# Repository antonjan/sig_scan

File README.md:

# sig_scan
This project will scan for rf signals and report them if there is signals detected using an rtl-sdr dongle on a a Raspberry Pi<br>
Libraery with exsyended frequency is avalable here https://github.com/librtlsdr/librtlsdr/tree/development<br>
## Pre Req libraeriies
    sudo apt-get install build-essential cmake git
    sudo apt-get install libusb-dev libusb-1.0-0-dev
    git clone https://github.com/librtlsdr/librtlsdr/tree/development
    cd librtlsdr
    git checkout development
    git status

    mkdir build && cd build
    cmake ../ -DINSTALL_UDEV_RULES=ON
    make

    sudo make install
    sudo ldconfig
# Setting up python 
    cd Documents/SX126X_LoRa_HAT_Code/raspberrypi/python/
## Sender 
    source ~/sdr-env/bin/activate
## Receiver
    source venv/bin/activate
# Running SIG Scanner
python gsm_scanner_new2.py

# Rafial R828D pin conections

    R828D (R820T-compatible) Pinout: Pin Number to Name

The R828D is usually supplied in a 32-pin QFN package. Here’s the most commonly reported pinout:

        Pin	Name	Function
        1	VCC	Power supply
        2	VCO	PLL VCO
        3	VCOIN	PLL VCO input
        4	VCOGND	PLL VCO ground
        5	VCOBUF	PLL VCO buffer output
        6	XIN	Crystal oscillator input
        7	XOUT	Crystal oscillator out
        8	VCC	Power supply
        9	GND	Ground
        10	AGC	Automatic Gain Control
        11	IFOUT	Intermediate Frequency Output
        12	VCC	Power supply
        13	GND	Ground
        14	RF_IN	RF Input (from antenna)
        15	GND	Ground
        16	NC	Not Connected
        17	VCC	Power supply
        18	NC	Not Connected
        19	LNA	Low Noise Amp control
        20	VCC	Power supply
        21	GND	Ground
        22	NC	Not Connected
        23	SDA	I²C Data
        24	SCL	I²C Clock
        25	GND	Ground
        26	VCC	Power supply
        27	NC	Not Connected
        28	VCC	Power supply
        29	NC	Not Connected
        30	NC	Not Connected
        31	NC	Not Connected
        32	NC	Not Connected
        30	NC	Not Connected
        31	NC	Not Connected
        32	NC	Not Connected
## Basic Connections

    Antenna → Matching Network → Pin 14 (RF_IN)
    Pin 11 (IFOUT) → RTL2832U IF Input
    Pin 23 (SDA) & Pin 24 (SCL) → RTL2832U I²C (for control)
    Pin 6 (XIN) & Pin 7 (XOUT) → 16 MHz Crystal (one end to XIN, other to XOUT, with load capacitors to GND)
    All VCC Pins → 3.3V Power
    All GND Pins → Ground Plane

## Register Map (Community Reference, RTL-SDR Driver)

The R828D is controlled via I²C. The register map is not openly published, but the rtl-sdr driver configures it as follows:

    I²C Address: 0x8C (write), 0x8D (read)
    Registers:
        Reg 0x00: Tuner enable, AGC, LNA setting
        Reg 0x01–0x05: PLL and frequency control
        Reg 0x06–0x0D: IF settings, filter bandwidth, gain stages
        Reg 0x0E–0x1F: Misc control, calibration, test modes

Example I²C Write Sequence for Initialization:
    
    uint8_t init_regs[] = {
    0x01, 0x16, 0xE0, 0x60, 0x40, // PLL settings
    0x20, 0x80, 0x40,             // IF gain, filter
    0xA1, 0x4B, 0x10              // AGC, LNA, etc.
    };
    i2c_write(R828D_ADDR, init_regs, sizeof(init_regs));
The actual values depend on frequency, IF, and gain requirements.
Refer to rtl-sdr tuner_r820t.c for full register programming examples. https://github.com/osmocom/rtl-sdr/blob/master/src/tuner_r820t.c

Step-by-Step Build Guide

    Connect RF_IN (Pin 14) to antenna/matching network.
    Connect IFOUT (Pin 11) to RTL2832U IF Input.
    Connect SDA (Pin 23) and SCL (Pin 24) to RTL2832U I²C bus. Use pull-up resistors (~4.7kΩ) to 3.3V.
    Connect 16 MHz crystal between XIN (Pin 6) and XOUT (Pin 7), with recommended load capacitors (~22pF) to ground.
    Connect all VCC pins to regulated 3.3V supply.
    Connect all GND pins to system ground.
    AGC (Pin 10) and LNA (Pin 19) can be controlled by RTL2832U or tied appropriately.
    Initialize R828D via I²C using register sequences from open-source drivers.
# R828 c driver 
https://github.com/osmocom/rtl-sdr/blob/master/src/tuner_r82xx.c

    Pin 10 (AGC) → RTL2832U AGC Output (optional, for gain control)
    Pin 19 (LNA) → Can be tied HIGH or controlled by RTL2832U for LNA operation

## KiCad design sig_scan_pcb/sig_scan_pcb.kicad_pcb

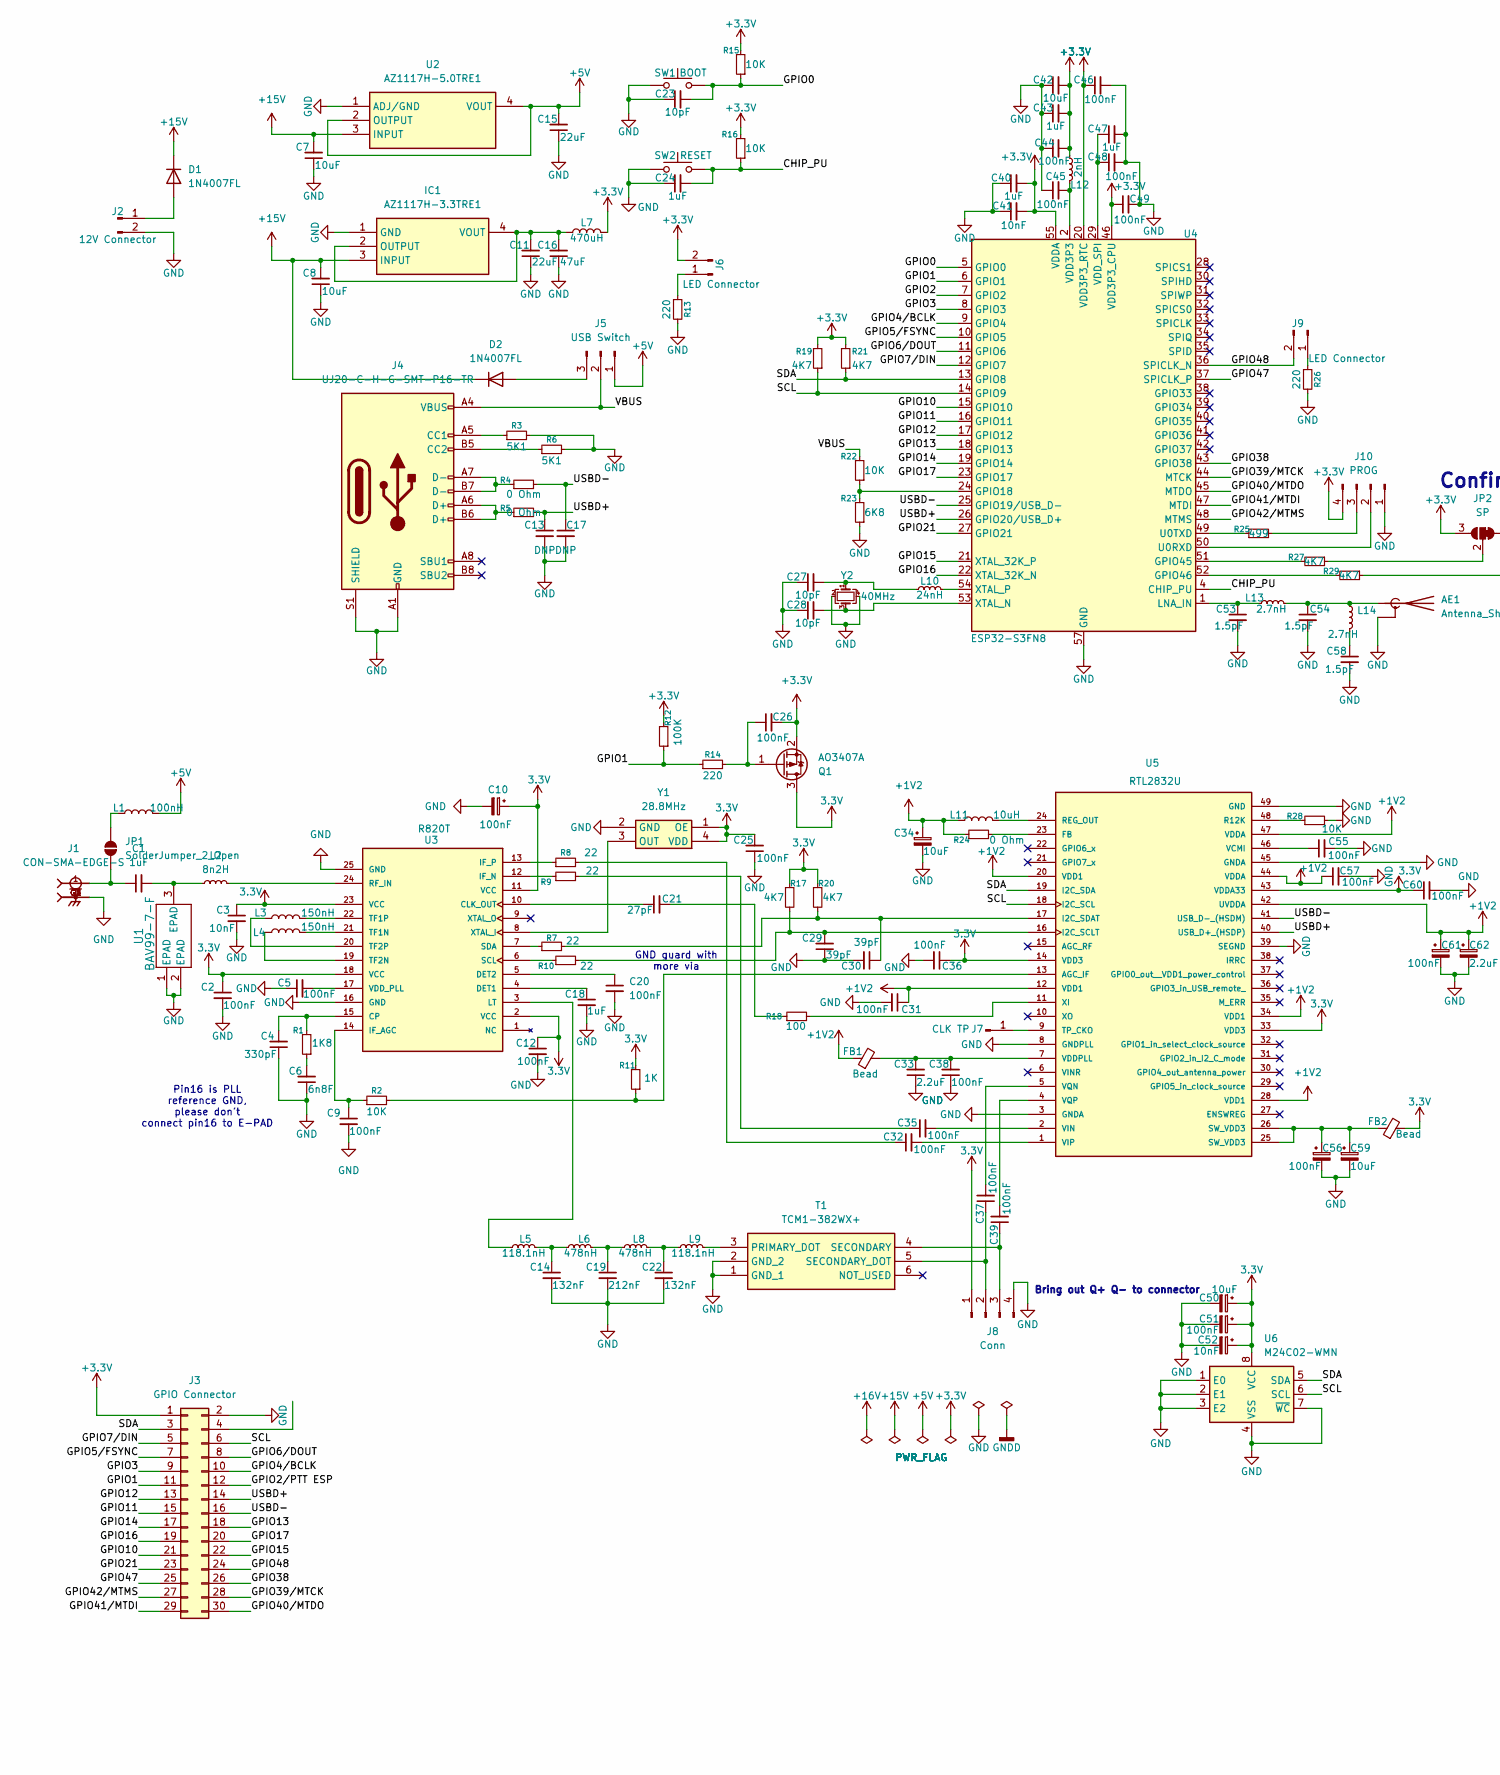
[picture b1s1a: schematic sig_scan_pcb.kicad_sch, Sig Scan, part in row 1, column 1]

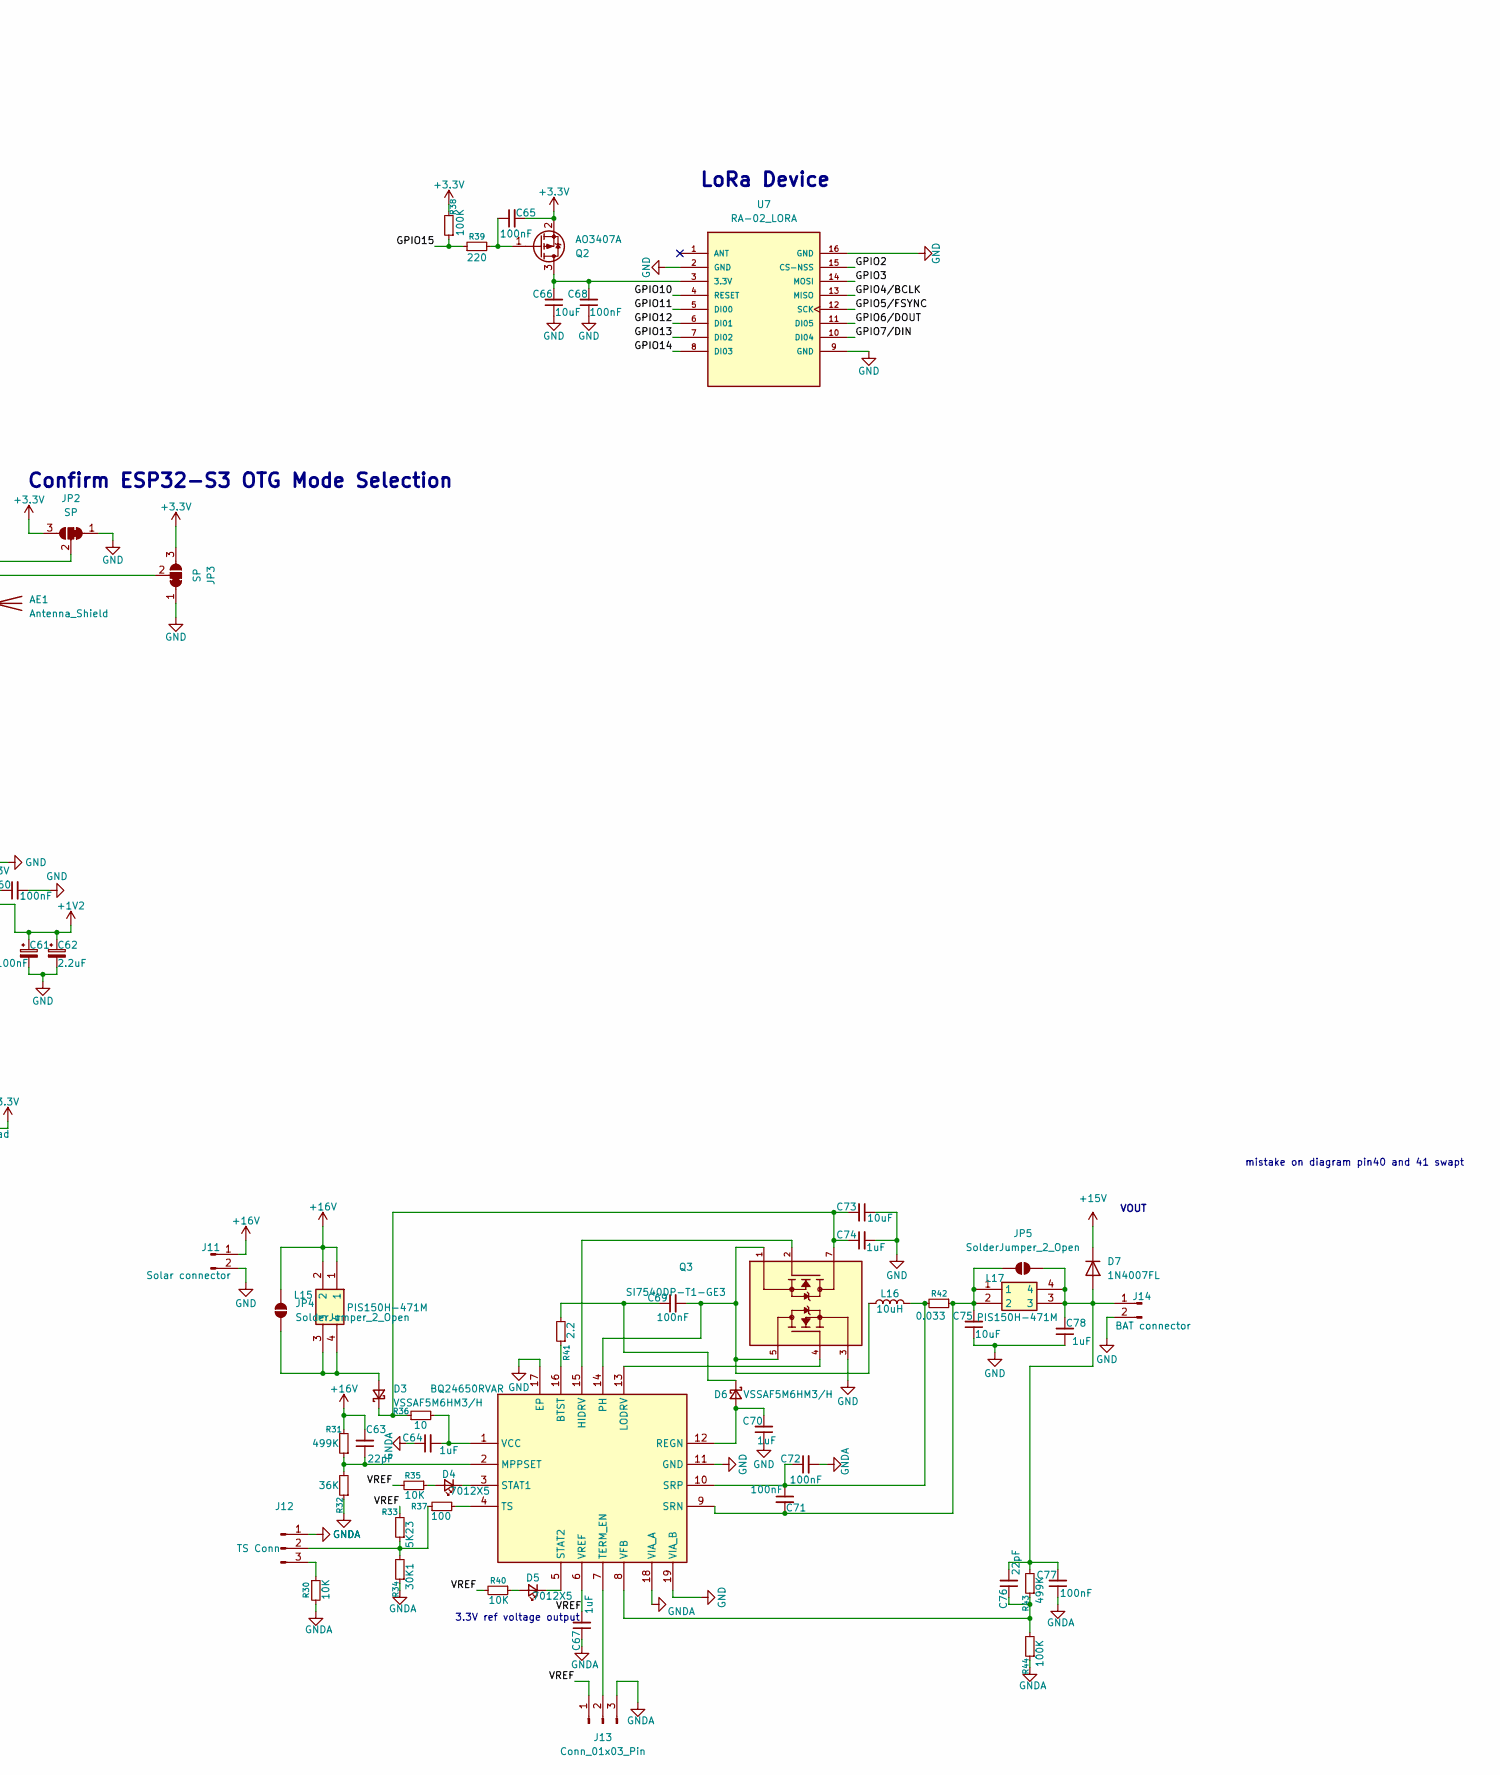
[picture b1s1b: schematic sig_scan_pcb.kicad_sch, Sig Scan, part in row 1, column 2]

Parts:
AE1: Antenna_Shield; Texas_SWRA117D_2.4GHz_Left
C1, C18, C24, C40, C43, C47, C64, C67, C70, C74, C78: 1uF; C_0805_2012Metric
C2, C5, C9, C10, C12, C20, C25, C26, C31, C32, C35, C36, C37, C38, C39, C44, C45, C46, C48, C49, C51, C55, C56, C57, C60, C61, C65, C68, C69, C71, C72, C77: 100nF; C_0805_2012Metric
C3, C41, C52: 10nF; C_0805_2012Metric
C4: 330pF; C_0805_2012Metric
C6: 6n8F; C_0805_2012Metric
C7, C8, C34, C42, C50, C59, C66, C73, C75: 10uF; C_0805_2012Metric
C11, C15: 22uF; C_0805_2012Metric
C13, C17: DNP; C_0805_2012Metric
C14, C22: 132nF; C_0805_2012Metric
C16: 47uF; C_1206_3216Metric
C19: 212nF; C_0805_2012Metric
C21: 27pF; C_0805_2012Metric
C23, C27, C28: 10pF; C_0805_2012Metric
C29, C30: 39pF; C_0805_2012Metric
C33, C62: 2.2uF; C_0805_2012Metric
C53, C54, C58: 1.5pF; C_0805_2012Metric
C63, C76: 22pF; C_0805_2012Metric
D1, D2, D7: 1N4007FL; D_SOD-123
D3, D6: VSSAF5M6HM3/H; D_SMA
D4, D5: 7012X5; LED_0805_2012Metric
FB1, FB2: Bead; C_0805_2012Metric
IC1: AZ1117H-3.3TRE1; SOT230P700X180-4N; Mouser Part Number 621-AZ1117H-3.3TRE1
IC2: BQ24650RVAR; QFN50P350X350X100-17N-D; Mouser Part Number 595-BQ24650RVAR
J1: CON-SMA-EDGE-S; RFSOLUTIONS_CON-SMA-EDGE-S; PARTREV 1
J2: 12V Connector; CUI_TB007-508-02BE
J3: GPIO Connector; PinHeader_2x15_P2.54mm_Vertical
J4: UJ20-C-H-G-SMT-P16-TR; USB_C_Receptacle_G-Switch_GT-USB-7010ASV
J5: USB Switch; PinHeader_1x03_P2.54mm_Vertical
J6, J9: LED Connector; PinHeader_1x02_P2.54mm_Vertical
J7: CLK TP; PinHeader_1x01_P2.54mm_Vertical
J8: Conn; PinHeader_1x04_P2.54mm_Vertical
J10: PROG; PinHeader_1x04_P2.54mm_Vertical
J11: Solar connector; CUI_TB007-508-02BE
J12: TS Conn; PinHeader_1x03_P2.54mm_Vertical
J13: Conn_01x03_Pin; SolderJumper-3_P1.3mm_Bridged12_RoundedPad1.0x1.5mm
J14: BAT connector; CUI_TB007-508-02BE
JP1, JP4, JP5: SolderJumper_2_Open; SolderJumper-2_P1.3mm_Open_RoundedPad1.0x1.5mm
JP2, JP3: SP; SolderJumper-3_P1.3mm_Bridged12_RoundedPad1.0x1.5mm
L1: 100nH; L_0805_2012Metric
L2: 8n2H; L_0805_2012Metric
L3, L4: 150nH; L_0805_2012Metric
L5, L9: 118.1nH; L_0603_1608Metric
L6, L8: 478nH; L_0603_1608Metric
L7: 470uH; SRR12604R7Y
L10: 24nH; L_0805_2012Metric
L11: 10uH; L_0805_2012Metric
L12: 2nH; L_0603_1608Metric
L13, L14: 2.7nH; L_0805_2012Metric
L15, L17: PIS150H-471M; PIS150H471M; Mouser Part Number 871-PIS150H-471M
L16: 10uH; IND_IHLP_2525_CZ_VIS
Q1, Q2: AO3407A; SOT-23
Q3: SI7540DP-T1-GE3; TRANS_SI7540DP-T1-GE3; PARTREV 16MAY13
R1: 1K8; R_0805_2012Metric
R2, R15, R16, R22, R28, R30, R35, R40: 10K; R_0805_2012Metric
R3, R6: 5K1; R_0805_2012Metric
R4, R5, R24: 0 Ohm; R_0805_2012Metric
R7, R8, R9, R10: 22; R_0805_2012Metric
R11: 1K; R_0805_2012Metric
R12, R38, R44: 100K; R_0805_2012Metric
R13, R14, R26, R39: 220; R_0805_2012Metric
R17, R19, R20, R21, R27, R29: 4K7; R_0805_2012Metric
R18, R37: 100; R_0805_2012Metric
R23: 6K8; R_0805_2012Metric
R25: 499; R_0805_2012Metric
R31, R43: 499K; R_0805_2012Metric
R32: 36K; R_0805_2012Metric
R33: 5K23; R_0805_2012Metric
R34: 30K1; R_0805_2012Metric
R36: 10; R_0805_2012Metric
R41: 2.2; R_0805_2012Metric
R42: 0.033; R_1206_3216Metric
SW1: BOOT; SW_Tactile_SPST_NO_Straight_CK_PTS636Sx25SMTRLFS
SW2: RESET; SW_Tactile_SPST_NO_Straight_CK_PTS636Sx25SMTRLFS
T1: TCM1-382WX+; TCM1382WX; Mouser Part Number 139-TCM1-382WX
U1: BAV99-7-F; SOT-23_DIO
U2: AZ1117H-5.0TRE1; SOT230P700X180-4N; Mouser Part Number 621-AZ1117H-5.0TRE1
U3: R820T; QFN50P400X400X90-25N; PARTREV 1.2
U4: ESP32-S3FN8; QFN-56-1EP_7x7mm_P0.4mm_EP4x4mm
U5: RTL2832U; QFN40P600X600X100-49N; PARTREV 1.4
U6: M24C02-WMN; SOIC-8_3.9x4.9mm_P1.27mm
U7: RA-02_LORA; MODULE_RA-02_LORA; PARTREV 2018/03/02
Y1: 28.8MHz; ATX11F32000MHZF05T; Mouser Part Number 815-ATX11F32000MF05T
Y2: 40MHz; ABM810000MHZ12D2W

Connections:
3.3V: C2.1, C3.1, C10.1, C12.1, C25.2, C36.1, C50.1, C51.1, C52.1, C60.1, FB2.2, J8.1, Q1.3 (D), R11.2, R17.1, R20.1, U3.2 (VCC), U3.11 (VCC), U3.18 (VCC), U3.23 (VCC), U5.14 (VDD3), U5.33 (VDD3), U5.43 (VDDA33), U6.8 (VCC), Y1.1 (OE), Y1.4 (VDD)
+1V2: C31.1, C34.1, C57.1, C61.1, C62.1, FB1.1, L11.1, R24.1, U5.12 (VDD1), U5.20 (VDD1), U5.28 (VDD1), U5.34 (VDD1), U5.42 (UVDDA), U5.44 (VDDA), U5.47 (VDDA)
+3.3V: C26.2, C40.2, C41.2, C42.2, C43.2, C44.2, C46.1, C49.1, C65.2, J3.1, J6.2, J10.4, JP2.3 (B), JP3.3 (B), L7.2, L12.1, Q1.2 (S), Q2.2 (S), R12.2, R15.2, R16.2, R19.2, R21.2, R38.2, U4.20 (VDD3P3_RTC), U4.46 (VDD3P3_CPU), U4.55 (VDDA), U4.56 (VDDA)
+5V: C15.2, J5.1, L1.2, U2.2 (OUTPUT), U2.4 (VOUT)
+15V: C7.2, C8.2, D1.1 (K), D2.1 (K), D7.1 (K), IC1.3 (INPUT), U2.3 (INPUT)
+16V: C63.2, J11.1, JP4.2 (B), L15.1, L15.2, R31.2
/CHIP_PU: C24.2, R16.1, SW2.2, U4.4 (CHIP_PU)
/GPIO0: C23.2, R15.1, SW1.2, U4.5 (GPIO0)
/GPIO1: J3.11, R12.1, R14.1, U4.6 (GPIO1)
/GPIO2: U4.7 (GPIO2), U7.15 (CS-NSS)
/GPIO3: J3.9, U4.8 (GPIO3), U7.14 (MOSI)
/GPIO4/BCLK: J3.10, U4.9 (GPIO4), U7.13 (MISO)
/GPIO5/FSYNC: J3.7, U4.10 (GPIO5), U7.12 (SCK)
/GPIO6/DOUT: J3.8, U4.11 (GPIO6), U7.11 (DI05)
/GPIO7/DIN: J3.5, U4.12 (GPIO7), U7.10 (DI04)
/GPIO10: J3.21, U4.15 (GPIO10), U7.4 (RESET)
/GPIO11: J3.15, U4.16 (GPIO11), U7.5 (DI00)
/GPIO12: J3.13, U4.17 (GPIO12), U7.6 (DI01)
/GPIO13: J3.18, U4.18 (GPIO13), U7.7 (DI02)
/GPIO14: J3.17, U4.19 (GPIO14), U7.8 (DI03)
/GPIO15: J3.22, R38.1, R39.1, U4.21 (XTAL_32K_P)
/GPIO16: J3.19, U4.22 (XTAL_32K_N)
/GPIO17: J3.20, U4.23 (GPIO17)
/GPIO21: J3.23, U4.27 (GPIO21)
/GPIO38: J3.26, U4.43 (GPIO38)
/GPIO39/MTCK: J3.28, U4.44 (MTCK)
/GPIO40/MTDO: J3.30, U4.45 (MTDO)
/GPIO41/MTDI: J3.29, U4.47 (MTDI)
/GPIO42/MTMS: J3.27, U4.48 (MTMS)
/GPIO47: J3.25, U4.37 (SPICLK_P)
/GPIO48: J3.24, J9.2, U4.36 (SPICLK_N)
/SCL: J3.6, R19.1, U4.14 (GPIO9), U5.18 (I2C_SCL), U6.6 (SCL)
/SDA: J3.3, R21.1, U4.13 (GPIO8), U5.19 (I2C_SDA), U6.5 (SDA)
/USBD+: C13.1, J3.14, R5.2, U4.26 (GPIO20/USB_D+), U5.40 (USB_D+_(HSDP))
/USBD-: C17.1, J3.16, R4.2, U4.25 (GPIO19/USB_D-), U5.41 (USB_D−_(HSDM))
/VBUS: J4.A4 (VBUS), J4.A9 (VBUS), J4.B4 (VBUS), J4.B9 (VBUS), J5.2, R22.2
/VREF: C67.2, IC2.6 (VREF), J13.1, R33.2, R35.2, R40.2
GND: AE1.2 (Shield), C2.2, C3.2, C4.1, C5.1, C6.1, C7.1, C8.1, C9.2, C10.2, C11.1, C12.2, C13.2, C14.2, C15.1, C16.1, C17.2, C18.2, C19.2, C20.2, C22.2, C23.1, C24.1, C25.1, C27.1, C28.1, C29.1, C30.2, C31.2, C33.1, C34.2, C36.2, C38.1, C40.1, C41.1, C42.1, C43.1, C44.1, C45.1, C46.2, C47.2, C48.2, C49.2, C50.2, C51.2, C52.2, C53.2, C54.2, C55.2, C56.2, C57.2, C58.2, C59.2, C60.2, C61.2, C62.2, C66.1, C68.1, C70.1, C73.1, C74.2, C75.1, C78.1, IC1.1 (GND), IC2.11 (GND), IC2.17 (EP), IC2.19 (VIA_B), J1.G1, J1.G2, J1.G3, J1.G4, J2.2, J3.2, J4.A1 (GND), J4.A12 (GND), J4.B1 (GND), J4.B12 (GND), J4.S1 (SHIELD), J8.4, J10.1, J11.2, J14.2, JP2.1 (A), JP3.1 (A), Q3.3, R3.2, R6.2, R13.2, R23.1, R26.2, R28.2, SW1.1, SW2.1, T1.1 (GND_1), T1.2 (GND_2), U1.1 (EPAD), U1.2 (EPAD), U2.1 (ADJ/GND), U3.16 (GND), U3.25 (GND), U4.57 (GND), U5.3 (GNDA), U5.8 (GNDPLL), U5.39 (SEGND), U5.45 (GNDA), U5.49 (GND), U6.1 (E0), U6.2 (E1), U6.3 (E2), U6.4 (VSS), U6.7 (~WC), U7.2 (GND), U7.9 (GND), U7.16 (GND), Y1.2 (GND), Y2.2, Y2.4
GNDA: C64.1, C67.1, C72.2, C77.1, IC2.18 (VIA_A), J12.1, J13.3, R30.2, R32.1, R34.1, R44.1
unnamed: AE1.1 (A), C54.1, L13.2, L14.1
unnamed: C1.2, L2.1, U1.3 (EPAD)
unnamed: C6.2, R1.1
unnamed: C14.1, L5.2, L6.1
unnamed: C19.1, L6.2, L8.1
unnamed: C21.2, R18.1
unnamed: C22.1, L8.2, L9.1
unnamed: C27.2, L10.1, Y2.1
unnamed: C32.1, R8.2
unnamed: C35.1, R9.2
unnamed: C45.2, L12.2, U4.2 (VDD3P3), U4.3 (VDD3P3)
unnamed: C56.1, C59.1, FB2.1, U5.25 (SW_VDD3), U5.26 (SW_VDD3)
unnamed: C58.1, L14.2
unnamed: D1.2 (A), J2.1
unnamed: D2.2 (A), J5.3
unnamed: D3.2 (A), JP4.1 (A), L15.3, L15.4
unnamed: C73.2, C74.1, D3.1 (K), Q3.7, Q3.8, Q3.9, R36.1
unnamed: D4.2 (A), R35.1
unnamed: D4.1 (K), IC2.3 (STAT1)
unnamed: D5.2 (A), R40.1
unnamed: D5.1 (K), IC2.5 (STAT2)
unnamed: C70.2, D6.2 (A), IC2.12 (REGN)
unnamed: C69.1, D6.1 (K), R41.2
unnamed: C76.2, C77.2, C78.2, D7.2 (A), J14.1, JP5.1 (A), L17.3, L17.4, R43.2
unnamed: C11.2, C16.2, IC1.2 (OUTPUT), IC1.4 (VOUT), L7.1
unnamed: IC2.16 (BTST), R41.1
unnamed: IC2.15 (HIDRV), Q3.2
unnamed: IC2.13 (LODRV), Q3.4
unnamed: C63.1, IC2.2 (MPPSET), R31.1, R32.2
unnamed: C69.2, IC2.14 (PH), L16.1, Q3.1, Q3.5, Q3.6, Q3.10
unnamed: C71.2, C75.2, IC2.9 (SRN), JP5.2 (B), L17.1, L17.2, R42.1
unnamed: C71.1, C72.1, IC2.10 (SRP), L16.2, R42.2
unnamed: IC2.7 (TERM_EN), J13.2
unnamed: IC2.4 (TS), R37.2
unnamed: C64.2, IC2.1 (VCC), R36.2
unnamed: C76.1, IC2.8 (VFB), R43.1, R44.2
unnamed: J4.A5 (CC1), R3.1
unnamed: J4.B5 (CC2), R6.1
unnamed: J4.A6 (D+), J4.B6 (D+), R5.1
unnamed: J4.A7 (D-), J4.B7 (D-), R4.1
unnamed: J6.1, R13.1
unnamed: J7.1, U5.9 (TP_CKO)
unnamed: C37.1, J8.2, T1.5 (SECONDARY_DOT)
unnamed: C39.1, J8.3, T1.4 (SECONDARY)
unnamed: J9.1, R26.1
unnamed: J10.2, U4.50 (U0RXD)
unnamed: J10.3, R25.2
unnamed: J12.2, R33.1, R34.2, R37.1
unnamed: J12.3, R30.1
unnamed: C1.1, J1.1, JP1.1 (A)
unnamed: JP1.2 (B), L1.1
unnamed: JP2.2 (C), R27.1
unnamed: JP3.2 (C), R29.1
unnamed: C26.1, Q1.1 (G), R14.2
unnamed: C66.2, C68.2, Q2.3 (D), U7.3 (3.3V)
unnamed: C65.1, Q2.1 (G), R39.2
unnamed: L9.2, T1.3 (PRIMARY_DOT)
unnamed: C21.1, U3.10 (CLK_OUT)
unnamed: C4.2, R1.2, U3.15 (CP)
unnamed: C18.1, U3.4 (DET1)
unnamed: C20.1, U3.5 (DET2)
unnamed: C9.1, R2.1, U3.14 (IF_AGC)
unnamed: R9.1, U3.12 (IF_N)
unnamed: R8.1, U3.13 (IF_P)
unnamed: L5.1, U3.3 (LT)
unnamed: L2.2, U3.24 (RF_IN)
unnamed: R10.1, U3.6 (SCL)
unnamed: R7.1, U3.7 (SDA)
unnamed: L4.2, U3.21 (TF1N)
unnamed: L3.2, U3.22 (TF1P)
unnamed: L4.1, U3.19 (TF2N)
unnamed: L3.1, U3.20 (TF2P)
unnamed: C5.2, U3.17 (VDD_PLL)
unnamed: U3.8 (XTAL_I), Y1.3 (OUT)
unnamed: R22.1, R23.2, U4.24 (GPIO18)
unnamed: R27.2, U4.51 (GPIO45)
unnamed: R29.2, U4.52 (GPIO46)
unnamed: C53.1, L13.1, U4.1 (LNA_IN)
unnamed: R25.1, U4.49 (U0TXD)
unnamed: C47.1, C48.1, U4.29 (VDD_SPI)
unnamed: C28.2, U4.53 (XTAL_N), Y2.3
unnamed: L10.2, U4.54 (XTAL_P)
unnamed: R2.2, R11.1, U5.13 (AGC_IF)
unnamed: R24.2, U5.23 (FB)
unnamed: C29.2, R10.2, R17.2, U5.16 (I2C_SCLT)
unnamed: C30.1, R7.2, R20.2, U5.17 (I2C_SDAT)
unnamed: R28.1, U5.48 (R12K)
unnamed: L11.2, U5.24 (REG_OUT)
unnamed: C55.1, U5.46 (VCMI)
unnamed: C33.2, C38.2, FB1.2, U5.7 (VDDPLL)
unnamed: C35.2, U5.2 (VIN)
unnamed: C32.2, U5.1 (VIP)
unnamed: C37.2, U5.5 (VQN)
unnamed: C39.2, U5.4 (VQP)
unnamed: R18.2, U5.11 (XI)

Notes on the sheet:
LoRa Device
Bring out Q+ Q- to connector
VOUT
3.3V ref voltage output
Pin16 is PLL reference GND, please don't connect pin16 to E-PAD
mistake on diagram pin40 and 41 swapt
GND guard with more via
Confirm ESP32-S3 OTG Mode Selection

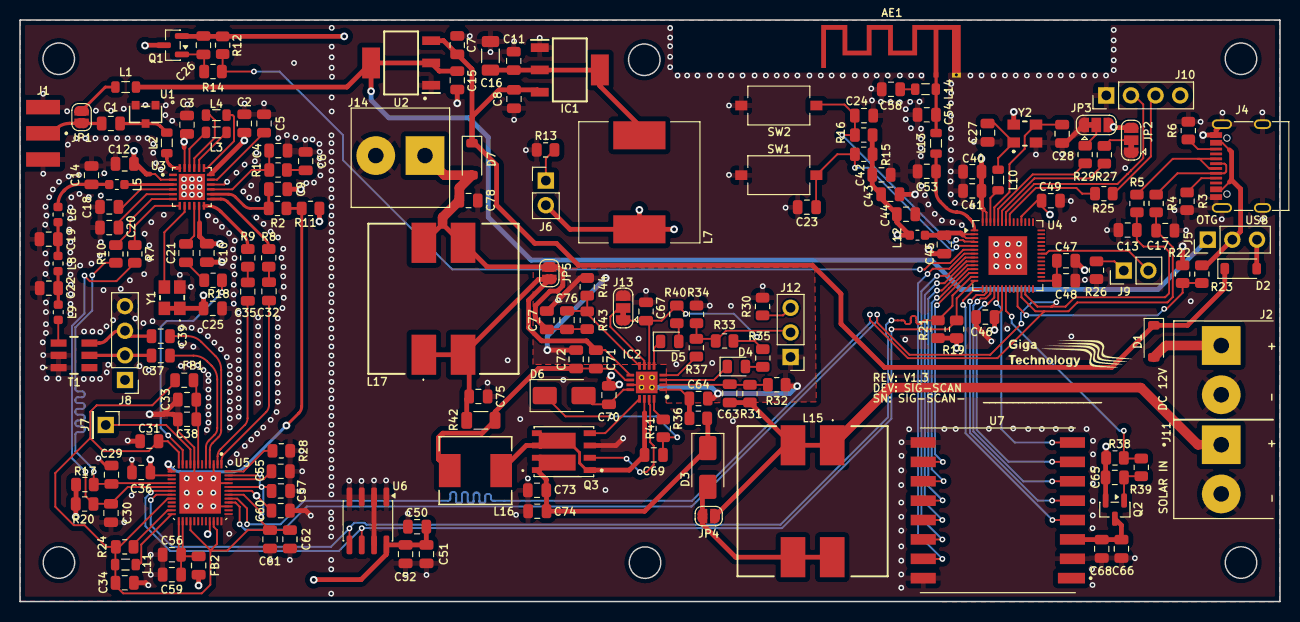
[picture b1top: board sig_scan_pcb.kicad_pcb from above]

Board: 4 copper layers, 130.0 x 60.0 mm, 184 parts (0 on the bottom side), 125 nets.

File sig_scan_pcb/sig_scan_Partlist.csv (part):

Id,Designator,Footprint,Quantity,Designation,Supplier and ref,
1,"C14,C22",C_0805_2012Metric,2,132nF,603-CC805KRX7R9BB124,https://www.mouser.co.za/ProductDetail/YAGEO/CC0805KRX7R9BB1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
2,"C15,C11",C_0805_2012Metric,2,22uF,187-CL21A226MAYNNNE ,https://www.mouser.co.za/ProductDetail/Samsung-Electro-Mecha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
3,C16,C_1206_3216Metric,1,47uF,80-C1206C476M8PAC,https://www.mouser.co.za/ProductDetail/KEMET/C1206C476M8PAC?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
4,C19,C_0805_2012Metric,1,212nF,187-CL21B224KBFNNNF,https://www.mouser.co.za/ProductDetail/Samsung-Electro-Mecha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
5,C21,C_0805_2012Metric,1,27pF,791-0805N270J631CT,https://www.mouser.co.za/ProductDetail/Walsin/0805N270J631CT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
6,"C24,C40,C67,C78,C64,C70,C1,C47,C74,C43,C18",C_0805_2012Metric,11,1uF,187-CL21B105KBFNNNE ,https://www.mouser.co.za/ProductDetail/Samsung-Electro-Mecha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
7,"C28,C23,C27",C_0805_2012Metric,3,10pF,80-C0805C100K5G ,https://www.mouser.co.za/ProductDetail/KEMET/C0805C100K5GACT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
8,"C29,C30",C_0805_2012Metric,2,39pF,791-0805N390J631CT,https://www.mouser.co.za/ProductDetail/Walsin/0805N390J631CT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
9,C4,C_0805_2012Metric,1,330pF,80-C0805C331J5G,https://www.mouser.co.za/ProductDetail/KEMET/C0805C331J5GACT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
10,"C41,C52,C3",C_0805_2012Metric,3,10nF,80-C0805C103K5R ,https://www.mouser.co.za/ProductDetail/KEMET/C0805C103K5RACT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
11,"C48,C20,C68,C77,C55,C45,C51,C37,C35,C60,C56,C61,C46,C2,C36,C10,C49,C69,C9,C25,C57,C44,C71,C32,C72,C39,C5,C65,C12,C31,C26,C38",C_0805_2012Metric,32,100nF,603-CC805KRX7R9BB104 ,https://www.mouser.co.za/ProductDetail/YAGEO/CC0805KRX7R9BB1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
12,"C53,C58,C54",C_0805_2012Metric,3,1.5pF,603-CC805CRNPO9BN1R5 ,https://www.mouser.co.za/ProductDetail/YAGEO/CC0805CRNPO9BN1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
13,"C59,C50,C8,C42,C7,C66,C34,C75,C73",C_0805_2012Metric,9,10uF,187-CL21A106KOQNNNG ,https://www.mouser.co.za/ProductDetail/Samsung-Electro-Mecha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
14,C6,C_0805_2012Metric,1,6n8F,791-0805B682K500CT,https://www.mouser.co.za/ProductDetail/Walsin/0805B682K500CT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
15,"C62,C33",C_0805_2012Metric,2,2.2uF,187-CL21B225KOFNNNG,https://www.mouser.co.za/ProductDetail/Samsung-Electro-Mecha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
16,"C76,C63",C_0805_2012Metric,2,22pF,80-C0805C220K5HACTU,https://www.mouser.co.za/ProductDetail/KEMET/C0805C220K5HACT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
17,"D5,D4",LED_0805_2012Metric,2,7012X5,606-7012X5,https://www.mouser.co.za/ProductDetail/VCC/7012X5?qs=I7nE1oQ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
18,"D6,D3",D_SMA,2,VSSAF5M6HM3/H,78-VSSAF5M6HM3/H,https://www.mouser.co.za/ProductDetail/Vishay-General-Semico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
19,"D7,D1,D2",D_SOD-123,3,MBR230LSFT1G,863-MBR230LSFT1G,https://www.mouser.co.za/ProductDetail/onsemi/MBR230LSFT1G?q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
20,"FB1,FB2",C_0805_2012Metric,2,Bead,810-MPZ2012S601AT000,https://www.mouser.co.za/ProductDetail/TDK/MPZ2012S601AT000?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
21,IC1,SOT230P700X180-4N,1,AZ1117H-3.3TRE1,621-AZ1117H-3.3TRE1,https://www.mouser.co.za/ProductDetail/Diodes-Incorporated/A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
22,IC2,QFN50P350X350X100-17N-D,1,BQ24650RVAR,595-BQ24650RVAR,https://www.mouser.co.za/ProductDetail/Texas-Instruments/BQ2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
23,J10,PinHeader_1x04_P2.54mm_Vertical,1,PROG,737-PH1-04-UA,https://www.mouser.co.za/ProductDetail/Adam-Tech/PH1-04-UA?q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
24,J11,CUI_TB007-508-02BE,1,Solar connector,737-EBQA-02-D-C,https://www.mouser.co.za/ProductDetail/Adam-Tech/EBQA-02-D-C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
25,J12,PinHeader_1x03_P2.54mm_Vertical,1,TS Conn,538-22-28-5032 ,https://www.mouser.co.za/ProductDetail/Molex/22-28-5032?qs=P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
26,J14,CUI_TB007-508-02BE,1,BAT connector,737-EBPA-02-D-C,https://www.mouser.co.za/ProductDetail/Adam-Tech/EBPA-02-D-C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
27,J2,CUI_TB007-508-02BE,1,12V Connector,737-EBQA-02-D-C,https://www.mouser.co.za/ProductDetail/Adam-Tech/EBQA-02-D-C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
28,J4,USB_C_Receptacle_G-Switch_GT-USB-7010ASV,1,UJ20-C-H-G-SMT-P16-TR,523-12402012E212A ,https://www.mouser.co.za/ProductDetail/Amphenol-Commercial-P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
29,J5,PinHeader_1x03_P2.54mm_Vertical,1,USB Switch,538-22-28-5032 ,https://www.mouser.co.za/ProductDetail/Molex/22-28-5032?qs=P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
30,"J6,J9",PinHeader_1x02_P2.54mm_Vertical,2,LED Connector,737-PH1-02-UA,https://www.mouser.co.za/ProductDetail/Adam-Tech/PH1-02-UA?q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
31,J7,PinHeader_1x01_P2.54mm_Vertical,1,CLK TP,,
32,J8,PinHeader_1x04_P2.54mm_Vertical,1,Conn,737-PH1-04-UA,https://www.mouser.co.za/ProductDetail/Adam-Tech/PH1-04-UA?q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
33,L1,L_0805_2012Metric,1,100nH,504-MCL2012V2-101-R,https://www.mouser.co.za/ProductDetail/Eaton-Electronics/MCL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
34,L10,L_0805_2012Metric,1,24nH,279-36502A24NJTDG ,https://www.mouser.co.za/ProductDetail/TE-Connectivity-Holsw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
35,L11,L_0805_2012Metric,1,10uH,963-LBR2012T100K,https://www.mouser.co.za/ProductDetail/TAIYO-YUDEN/LBR2012T1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
36,L12,L_0603_1608Metric,1,2nH,279-36550603S2N0T,https://www.mouser.co.za/ProductDetail/TE-Connectivity-Sigma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
37,"L14,L13",L_0805_2012Metric,2,2.7nH,815-AIMC-0805-2N7ST,https://www.mouser.co.za/ProductDetail/ABRACON/AIMC-0805-2N7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
38,"L15,L17",PIS150H471M,2,PIS150H-471M,871-PIS150H-471M,https://www.mouser.co.za/ProductDetail/EPCOS-TDK/PIS150H-471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
39,L16,IND_IHLP_2525_CZ_VIS,1,10uH,70-IHLP2525CZER100M0,https://www.mouser.co.za/ProductDetail/Vishay-Dale/IHLP2525C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
40,L2,L_0805_2012Metric,1,8n2H,70-IMC0805ER6N8J01,https://www.mouser.co.za/ProductDetail/Vishay-Dale/IMC0805ER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
41,"L4,L3",L_0805_2012Metric,2,150nH,704-MCQ1V2012-R150-R,https://www.mouser.co.za/ProductDetail/Eaton-Electronics/MCQ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
42,"L5,L9",L_0603_1608Metric,2,118.1nH,704-MCQ1V1608-R120-R,https://www.mouser.co.za/ProductDetail/Eaton-Electronics/MCQ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
43,"L6,L8",L_0603_1608Metric,2,478nH,81-LQW18CAR48J00D,https://www.mouser.co.za/ProductDetail/Murata-Electronics/LQ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
44,L7,SRR12604R7Y,1,470uH,652-SRR1260-4R7Y,https://www.mouser.co.za/ProductDetail/Bourns/SRR1260-4R7Y?q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
45,"Q1,Q2",SOT-23,2,AO3407A,942-IRLML9301TRPBF,https://www.mouser.co.za/ProductDetail/Infineon-Technologies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
46,Q3,TRANS_SI7540DP-T1-GE3,1,SI7540DP-T1-GE3,78-SI7540ADP-T1-GE3,https://www.mouser.co.za/ProductDetail/Vishay-Semiconductors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
47,R1,R_0805_2012Metric,1,1K8,603-RT0805DRE071K8L,https://www.mouser.co.za/ProductDetail/YAGEO/RT0805DRE071K8L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
48,"R10,R9,R7,R8",R_0805_2012Metric,4,22,603-RT0805FRE0722RL,https://www.mouser.co.za/ProductDetail/YAGEO/RT0805FRE0722RL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
49,R11,R_0805_2012Metric,1,1K,603-RT0805DRD071KL ,https://www.mouser.co.za/ProductDetail/YAGEO/RT0805DRD071KL?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
50,"R16,R2,R30,R40,R35,R22,R28,R15",R_0805_2012Metric,8,10K,660-RN73R2ATD1002D25 ,https://www.mouser.co.za/ProductDetail/KOA-Speer/RN73R2ATTD1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
51,"R18,R37",R_0805_2012Metric,2,100,754-RR1220P-101D,https://www.mouser.co.za/ProductDetail/Susumu/RR1220P-101-D?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
52,"R19,R27,R20,R21,R17,R29",R_0805_2012Metric,6,4K7,754-RG2012P-472DT5 ,https://www.mouser.co.za/ProductDetail/Susumu/RG2012P-472-D-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
53,R23,R_0805_2012Metric,1,6K8,667-ERA-6AED682V,https://www.mouser.co.za/ProductDetail/Panasonic/ERA-6AED682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
54,"R24,R4,R5",R_0805_2012Metric,3,0 Ohm,594-MCU0805MZ0000ZP5 ,https://www.mouser.co.za/ProductDetail/Vishay-Beyschlag/MCU0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
55,R25,R_0805_2012Metric,1,499,603-RT0805FRD07499RL ,https://www.mouser.co.za/ProductDetail/YAGEO/RT0805FRD07499R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
56,"R26,R14,R39,R13",R_0805_2012Metric,4,220,667-ERA-6AEB221V,https://www.mouser.co.za/ProductDetail/Panasonic/ERA-6AEB221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
57,"R3,R6",R_0805_2012Metric,2,5K1,754-RR1220P-512D,https://www.mouser.co.za/ProductDetail/Susumu/RR1220P-512-D?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
58,"R31,R43",R_0805_2012Metric,2,499K,667-ERA-6AEB4993V,https://www.mouser.co.za/ProductDetail/Panasonic/ERA-6AEB499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
59,R32,R_0805_2012Metric,1,36K,603-RT0805FRE0736KL,https://www.mouser.co.za/ProductDetail/YAGEO/RT0805FRE0736KL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
60,R33,R_0805_2012Metric,1,5K23,667-ERA-6AEB5231V,https://www.mouser.co.za/ProductDetail/Panasonic/ERA-6AEB523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
61,R34,R_0805_2012Metric,1,30K1,603-RT0805DRE0730K1L,https://www.mouser.co.za/ProductDetail/YAGEO/RT0805DRE0730K1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
62,R36,R_0805_2012Metric,1,10,603-RT0805FRE1310RL,https://www.mouser.co.za/ProductDetail/YAGEO/RT0805FRE1310RL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
63,R41,R_0805_2012Metric,1,2.2,71-TNPW08052R20DEEA,https://www.mouser.co.za/ProductDetail/Vishay/TNPW08052R20DE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
64,R42,R_1206_3216Metric,1,0.033,667-ERJ-8BWFR033V,https://www.mouser.co.za/ProductDetail/Panasonic/ERJ-8BWFR03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
65,"R44,R12,R38",R_0805_2012Metric,3,100K,603-RT0805DRE07100KL,https://www.mouser.co.za/ProductDetail/YAGEO/RT0805DRE07100K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

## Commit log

2025-04-10 Update README.md
    adding compilation details
2025-05-22 working GSM scanner
2025-05-30 Adding files to restore USB to LoRa device
2025-05-30 Updating README file
2025-06-29 Adding python code for LoRa webserver
2025-06-30 similated webserver
2025-07-02 Adding Pi file with all necessary working python scripts and webserver folders
2025-07-04 Updating LoRa Pi python codes and adding audio files
2025-07-28 Adding LoRa Wifi setup document
2025-07-28 Adding LoRa Wifi setup word doc
2025-07-28 added image
2025-08-27 adding the kicad project
2025-08-30 adding uncompleet rtl-sdr design
2025-10-10 almost compleet design needs psu
2025-11-27 Updating PCB to final design and updating partlist
2025-12-01 Adding Gerber files
2025-12-01 Adding Gerber zip file
2025-12-05 Updating Gerber files with correct clearances
2025-12-05 3d view of PCB
2026-01-07 Updating ground planes for solar chip and updating Gerber files
2026-01-08 Adding fixed isolation to gerber files

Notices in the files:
sig_scan_pcb/sig_scan_pcb.kicad_pcb:
All rights reserved
